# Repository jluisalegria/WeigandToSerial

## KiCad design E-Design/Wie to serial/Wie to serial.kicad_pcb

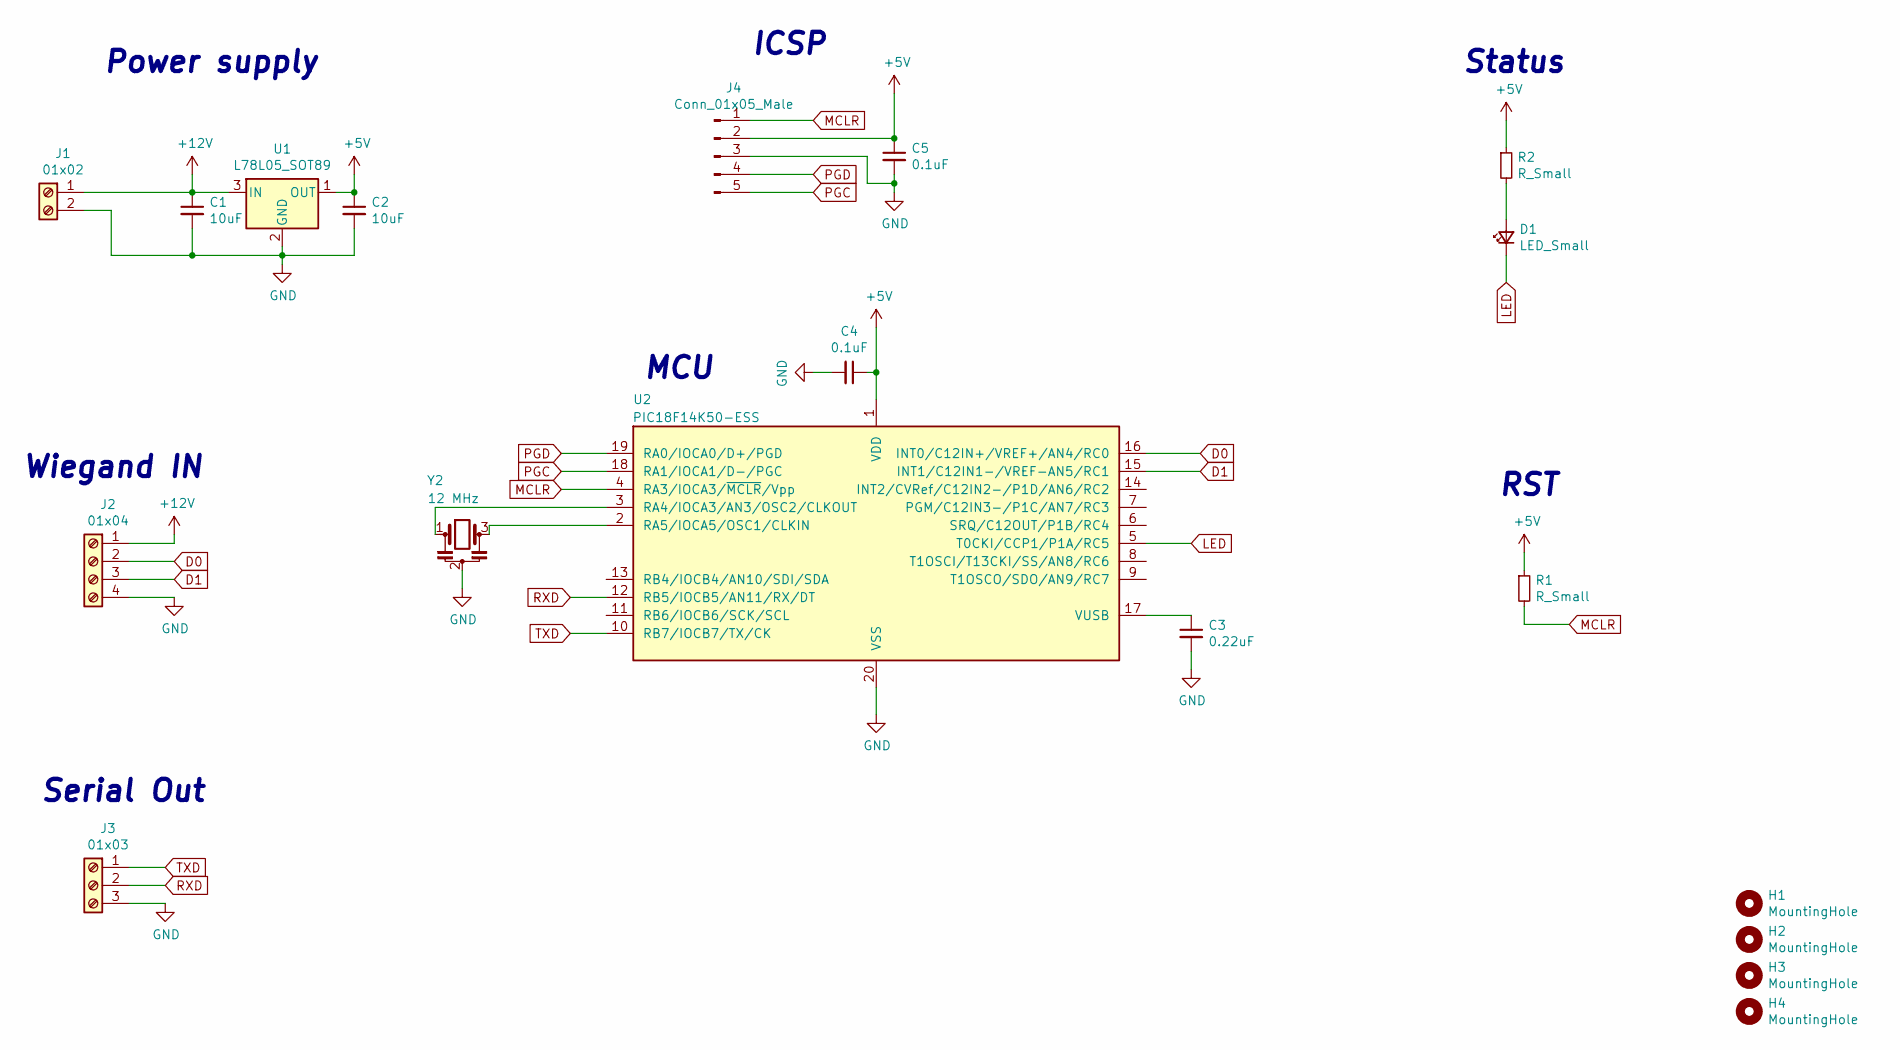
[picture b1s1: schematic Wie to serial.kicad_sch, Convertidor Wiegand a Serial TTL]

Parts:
C1, C2: 10uF; C_0805_2012Metric_Pad1.18x1.45mm_HandSolder; LCSC C40894
C3: 0.22uF; C_0805_2012Metric_Pad1.18x1.45mm_HandSolder; LCSC C13967
C4, C5: 0.1uF; C_0805_2012Metric_Pad1.18x1.45mm_HandSolder; LCSC C1790
D1: LED_Small; LED_0805_2012Metric_Pad1.15x1.40mm_HandSolder; LCSC C84256
H1, H2, H3, H4: MountingHole; MountingHole_3.2mm_M3_DIN965
J1: 01x02; TerminalBlock_4Ucon_1x02_P3.50mm_Horizontal; LCSC C784942
J2: 01x04; TerminalBlock_4Ucon_1x04_P3.50mm_Horizontal; LCSC C557656
J3: 01x03; TerminalBlock_4Ucon_1x03_P3.50mm_Horizontal; LCSC C557655
J4: Conn_01x05_Male; PinHeader_1x05_P2.54mm_Vertical
R1: R_Small; R_0805_2012Metric_Pad1.20x1.40mm_HandSolder; LCSC C17414
R2: R_Small; R_0805_2012Metric_Pad1.20x1.40mm_HandSolder; LCSC C17630
U1: L78L05_SOT89; SOT-89-3; Part Number LR2010B-M50; LCSC C459773
U2: PIC18F14K50-ESS; SSOP-20_5.3x7.2mm_P0.65mm; LCSC C12460
Y2: 12 MHz; Resonator_SMD_muRata_CSTxExxV-3Pin_3.0x1.1mm; Part Number CSTNE12M0G52Z000R0; LCSC C907940

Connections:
+5V: C2.1, C4.1, C5.1, J4.2, R1.1, R2.1, U1.1 (OUT), U2.1 (VDD)
+12V: C1.1, J1.1, J2.1, U1.3 (IN)
D0: J2.2, U2.16 (INT0/C12IN+/VREF+/AN4/RC0)
D1: J2.3, U2.15 (INT1/C12IN1-/VREF-AN5/RC1)
GND: C1.2, C2.2, C3.2, C4.2, C5.2, J1.2, J2.4, J3.3, J4.3, U1.2 (GND), U2.20 (VSS), Y2.2
LED: D1.1 (K), U2.5 (T0CKI/CCP1/P1A/RC5)
MCLR: J4.1, R1.2, U2.4 (RA3/IOCA3/~MCLR/Vpp)
unnamed: C3.1, U2.17 (VUSB)
unnamed: D1.2 (A), R2.2
unnamed: U2.2 (RA5/IOCA5/OSC1/CLKIN), Y2.3
unnamed: U2.3 (RA4/IOCA3/AN3/OSC2/CLKOUT), Y2.1
PGC: J4.5, U2.18 (RA1/IOCA1/D-/PGC)
PGD: J4.4, U2.19 (RA0/IOCA0/D+/PGD)
RXD: J3.2, U2.12 (RB5/IOCB5/AN11/RX/DT)
TXD: J3.1, U2.10 (RB7/IOCB7/TX/CK)

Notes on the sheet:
Status
MCU
Serial Out
Wiegand IN
ICSP
Power supply
RST

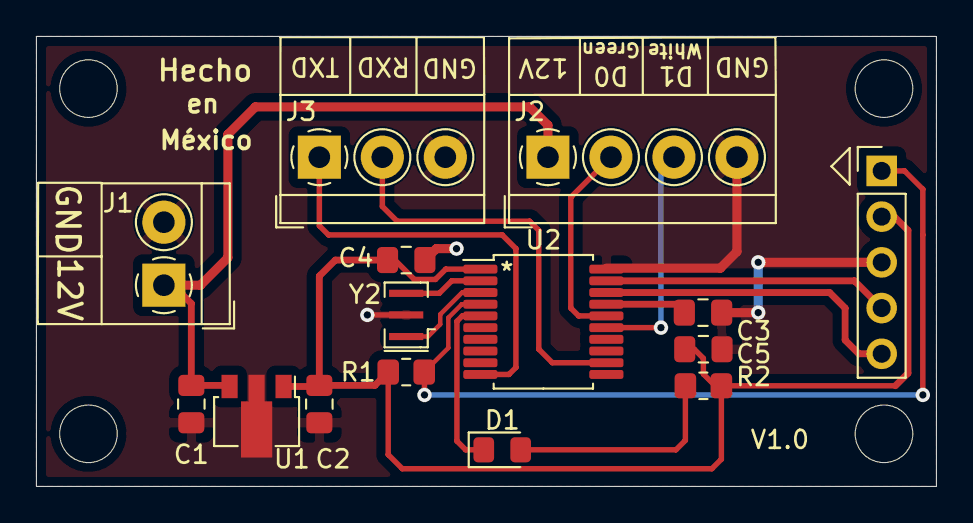
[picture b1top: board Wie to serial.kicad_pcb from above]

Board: 2 copper layers, 50.0 x 25.0 mm, 19 parts (0 on the bottom side), 15 nets.

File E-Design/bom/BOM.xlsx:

Comment | Designator | Footprint | JLCPCB Part #（optional）
10uF | C1, C2 | Capacitor_SMD:C_0805_2012Metric_Pad1.18x1.45mm_HandSolder | C40894
0.22uF | C3 | Capacitor_SMD:C_0805_2012Metric_Pad1.18x1.45mm_HandSolder | C13967
0.1uF | C4, C5 | Capacitor_SMD:C_0805_2012Metric_Pad1.18x1.45mm_HandSolder | C1790
LED_Small | D1 | LED_SMD:LED_0805_2012Metric_Pad1.15x1.40mm_HandSolder | C84256
MountingHole | H1, H2, H3, H4 | MountingHole:MountingHole_3.2mm_M3_DIN965 | -
01x02 | J1 | TerminalBlock_4Ucon:TerminalBlock_4Ucon_1x02_P3.50mm_Horizontal | C784942
01x04 | J2 | TerminalBlock_4Ucon:TerminalBlock_4Ucon_1x04_P3.50mm_Horizontal | C557656
01x03 | J3 | TerminalBlock_4Ucon:TerminalBlock_4Ucon_1x03_P3.50mm_Horizontal | C557655
Conn_01x05_Male | J4 | Connector_PinHeader_2.54mm:PinHeader_1x05_P2.54mm_Vertical | -
R_Small | R1, R2 | Resistor_SMD:R_0805_2012Metric_Pad1.20x1.40mm_HandSolder | C17414
L78L05_SOT89 | U1 | Package_TO_SOT_SMD:SOT-89-3 | C459773
PIC18F14K50-ESS | U2 | Package_SO:SSOP-20_5.3x7.2mm_P0.65mm | C12460
12 MHz | Y2 | Crystal:Resonator_SMD_muRata_CSTxExxV-3Pin_3.0x1.1mm | C907940

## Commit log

2023-05-10 Addes image files
2023-05-10 Move DIR for e design
2023-08-21 Added gitignore
